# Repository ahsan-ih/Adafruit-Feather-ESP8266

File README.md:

## Adafruit Feather HUZZAH with ESP8266 - Loose Headers PCB

**DISCLAIMER:**: The original creators of the Adafruit Feather HUZZAH with ESP8266 are [Adafruit.com](https://www.adafruit.com). The development has been presented in the given repository just for demonstration purposes.

PCB files for the Adafruit Feather HUZZAH with ESP8266 - Loose Headers. Format is EagleCAD schematic and board layout

- https://www.adafruit.com/product/2821

### Description

Feather is the new development board from Adafruit, and like its namesake it is thin, light, and lets you fly! We designed Feather to be a new standard for portable microcontroller cores.

This is the **Adafruit Feather HUZZAH ESP8266** - our take on an 'all-in-one' ESP8266 WiFi development board with built in USB and battery charging. Its an ESP8266 WiFi module with all the extras you need, ready to rock! [We have other boards in the Feather family, check'em out here.](https://www.adafruit.com/feather)

At the Feather HUZZAH's heart is an ESP8266 WiFi microcontroller clocked at 80 MHz and at 3.3V logic. This microcontroller contains a Tensilica chip core as well as a full WiFi stack. You can program the microcontroller using the Arduino IDE for an easy-to-run Internet of Things core. We wired up a high-quality SiLabs CP2104 USB-Serial chip that can upload code at a blistering 921600 baud for fast development time. It also has auto-reset so no noodling with pins and reset button pressings. The CP2104 has better driver support than the CH340 and can do very high speeds without stability issues.

To make it easy to use for portable projects, we added a connector for any of our 3.7V Lithium polymer batteries and built in battery charging. You don't need a battery, it will run just fine straight from the micro USB connector. But, if you do have a battery, you can take it on the go, then plug in the USB to recharge. The Feather will automatically switch over to USB power when its available.

**Here's some handy specs!**

- Measures 2.0" x 0.9" x 0.28" (51mm x 23mm x 8mm) without headers soldered in
- Light as a (large?) feather - 9.7 grams
- ESP8266 @ 80MHz with 3.3V logic/power
- 4MB of FLASH (32 MBit)
- Built in WiFi 802.11 b/g/n
- 3.3V regulator with 500mA peak current output
- CP2104 USB-Serial converter onboard with 921600 max baudrate for speedy uploading
- Auto-reset support for getting into bootload mode before firmware upload
- 9 x GPIO pins - can also be used as I2C and SPI
- 1 x analog inputs 1.0V max
- Built in 100mA LiPoly charger with charging status indicator LED, can also cut a trace to disable the charger
- Pin #0 red LED for general purpose blinking. Pin #2 blue LED for bootloading debug & general purpose blinking
- Power/enable pin
- 4 mounting holes
- Reset button
  Comes fully assembled and tested, with a USB interface that lets you quickly use it with the Arduino IDE or NodeMCU Lua (it comes preprogrammed with the Lua interpreter). We also toss in some headers so you can solder it in and plug into a solderless breadboard. **Lipoly battery and USB cable not included** (but we do have lots of options in the shop if you'd like!)

[Check out our tutorial for all sorts of details, including schematics, files, IDE instructions, power management and more!](https://learn.adafruit.com/adafruit-feather-huzzah-esp8266)

### License

Adafruit invests time and resources providing this open source design, please support Adafruit and open-source hardware by purchasing products from [Adafruit](https://www.adafruit.com)!

Designed by Limor Fried/Ladyada for Adafruit Industries.

Creative Commons Attribution/Share-Alike, all text above must be included in any redistribution. See license.txt for additional details.

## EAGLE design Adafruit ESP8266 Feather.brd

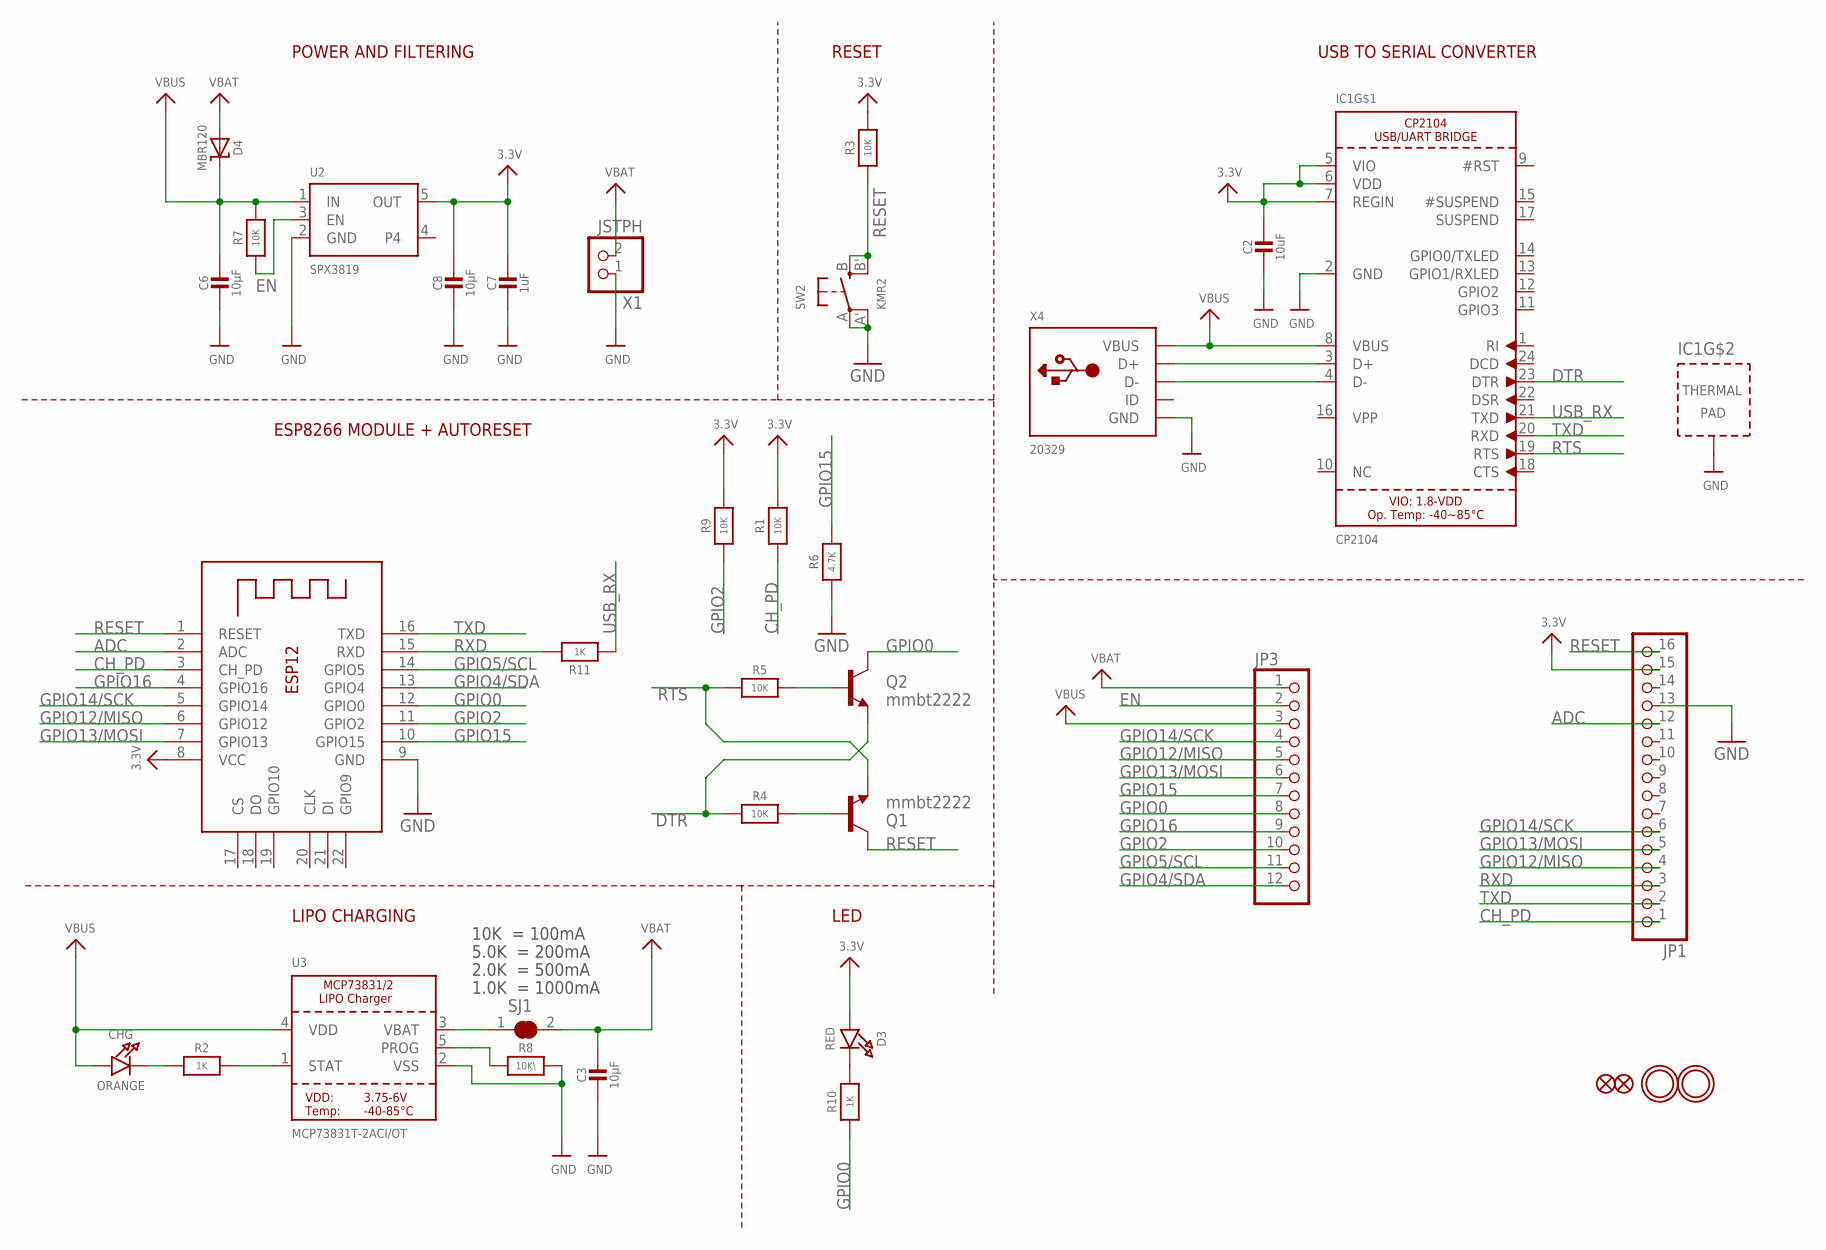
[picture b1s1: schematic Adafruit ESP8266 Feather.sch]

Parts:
C2: 10uF; 0805-NO
C3, C6, C8: 10µF; 0805-NO
C7: 1uF; 0603-NO
CHG: ORANGE; CHIPLED_0805_NOOUTLINE
D3: RED; CHIPLED_0805_NOOUTLINE
D4: MBR120; SOD-123
IC1: CP2104; QFN24_4MM_SMSC
JP1: HEADER-1X16ROUND; 1X16_ROUND
JP3: HEADER-1X12; 1X12_ROUND
Q1, Q2: mmbt2222; SOT23-3
R1, R3, R4, R7, R9: 10K; 0603-NO
R2, R10: 1K; 0603-NO
R5: 10K; _0603MP
R6: 4.7K; 0603-NO
R8: 10K\; 0603-NO
R11: 1K; _0603MP
SJ1: SOLDERJUMPER_CLOSED; SOLDERJUMPER_CLOSEDWIRE
SW2: KMR2; BTN_KMR2_4.6X2.8
U2: SPX3819; SOT23-5
U3: MCP73831T-2ACI/OT; SOT23-5
U$31, U$32: MOUNTINGHOLE2.5; MOUNTINGHOLE_2.5_PLATED
U$34, U$35: FIDUCIAL""; FIDUCIAL_1MM
X1: JSTPH; JSTPH2
X2: ESP-12; ESP-12E
X4: 20329; 4UCONN_20329_V2

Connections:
3.3V: C2.1, C7.1, C8.1, D3.A, IC1.5 (VIO), IC1.6 (VDD), IC1.7 (REGIN), JP1.15, R1.2, R3.2, R9.2, U2.5 (OUT), X2.8 (VCC)
ADC: JP1.12, X2.2 (ADC)
CH_PD: JP1.1, R1.1, X2.3 (CH_PD)
DTR: IC1.23 (DTR), Q2.2 (E), R4.1
EN: JP3.2, R7.1, U2.3 (EN)
GND: C2.2, C3.2, C6.2, C7.2, C8.2, IC1.2 (GND), IC1.THERM (TP), JP1.13, R6.1, R8.2, SW2.A, SW2.A' (P1), U2.2 (GND), U3.2 (VSS), X1.1, X2.9 (GND), X4.BASE@1 (GND), X4.BASE@2 (GND), X4.GND, X4.SPRT@1 (GND), X4.SPRT@2 (GND), X4.SPRT@3 (GND), X4.SPRT@4 (GND)
GPIO0: JP3.8, Q2.3 (C), R10.1, X2.12 (GPIO0)
GPIO2: JP3.10, R9.1, X2.11 (GPIO2)
GPIO4/SDA: JP3.12, X2.13 (GPIO4)
GPIO5/SCL: JP3.11, X2.14 (GPIO5)
GPIO12/MISO: JP1.4, JP3.5, X2.6 (GPIO12)
GPIO13/MOSI: JP1.5, JP3.6, X2.7 (GPIO13)
GPIO14/SCK: JP1.6, JP3.4, X2.5 (GPIO14)
GPIO15: JP3.7, R6.2, X2.10 (GPIO15)
GPIO16: JP3.9, X2.4 (GPIO16)
unnamed: CHG.C, R2.1
unnamed: IC1.3 (D+), X4.D+
unnamed: R2.2, U3.1 (STAT)
unnamed: R8.1, U3.5 (PROG)
unnamed: D3.C, R10.2
unnamed: IC1.4 (D-), X4.D-
unnamed: SJ1.1, U3.3 (VBAT)
unnamed: Q1.1 (B), R4.2
unnamed: Q2.1 (B), R5.2
RESET: JP1.16, Q1.3 (C), R3.1, SW2.B (S), SW2.B' (S1), X2.1 (RESET)
RTS: IC1.19 (RTS), Q1.2 (E), R5.1
RXD: JP1.3, R11.2, X2.15 (RXD)
TXD: IC1.20 (RXD), JP1.2, X2.16 (TXD)
USB_RX: IC1.21 (TXD), R11.1
VBAT: C3.1, D4.A, JP3.1, SJ1.2, X1.2
VBUS: C6.1, CHG.A, D4.C, IC1.8 (VBUS), JP3.3, R7.2, U2.1 (IN), U3.4 (VDD), X4.VBUS

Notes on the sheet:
POWER AND FILTERING
RESET
10K = 100mA
5.0K = 200mA
2.0K = 500mA
1.0K = 1000mA
USB TO SERIAL CONVERTER
LIPO CHARGING
LED
ESP8266 MODULE + AUTORESET

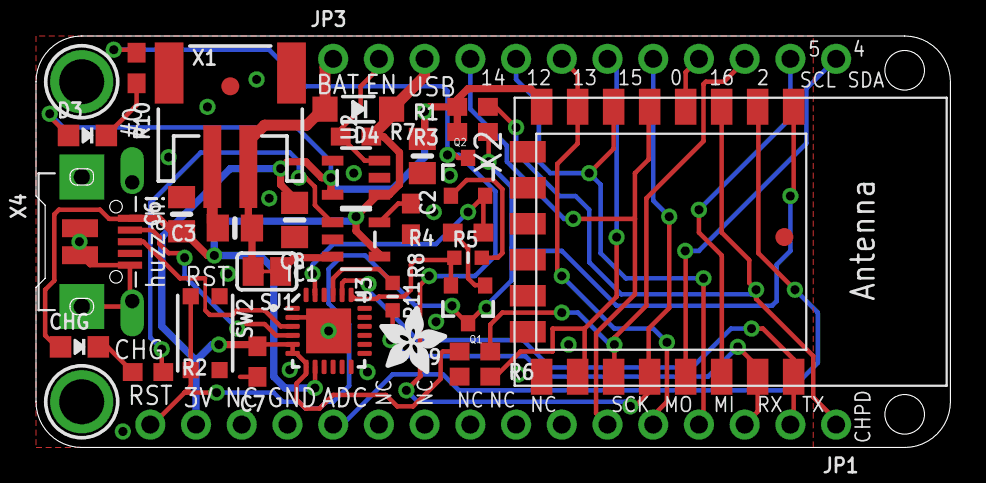
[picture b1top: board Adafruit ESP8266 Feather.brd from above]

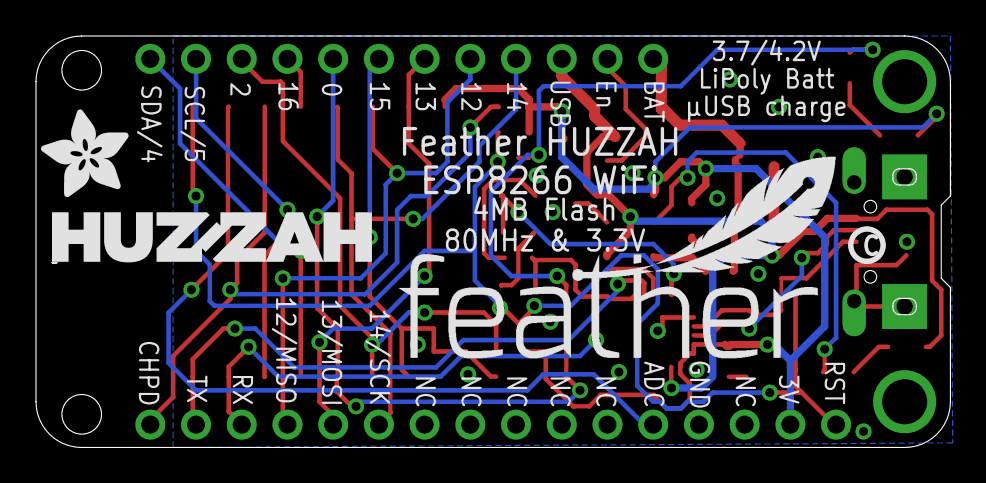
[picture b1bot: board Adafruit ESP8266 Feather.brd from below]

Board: 2 copper layers, 50.8 x 22.9 mm, 40 parts (4 on the bottom side), 31 nets.

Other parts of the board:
U$7: ADAFRUIT_5MM
U$9: FEATHERLOGO
U$13: PCBFEAT-REV-040
U$15: ADAFRUIT_3.5MM
U$23: HUZZAHLOGO

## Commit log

2020-03-01 Added components to the schematic & placed footprints in board layout
2020-03-01 Finished Schematic: CP2104 + SPX3819 + MCP73831T-2ACI/OT + KMR2(Reset)
2020-03-01 Schematic: ESP8266 + (JP1 + JP3 I/O Headers)
2020-03-01 Traces Top: ESP8266 Unrouted
2020-03-01 Feather .Brd: minor adjustments
2020-03-01 Feather .Brd: completed the layout design

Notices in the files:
parts and their libraries:
microbuilder: This work is placed in the public domain, and may be freely used for commercial and non-commercial work with the following conditions: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
SparkFun: Licensing: CC v3.0 Share-Alike You are welcome to use this library for commercial purposes.
